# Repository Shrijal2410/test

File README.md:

# Bionic Arm

Our project aims to provide a realistic, functional prosthetic hand for those who have lost theirs. We're not delving into mastering neurology; instead, we're focusing on using muscle sensor data (EMG) to control the hand's movements. Our design is intended for individuals with sufficient remaining limb functionality to provide us with EMG signals, allowing us to move the fingers and wrist accordingly.

## Objectives
Simple enough to outline, but challenging to achieve:

- Create a functional hand with full control over five fingers and wrist movement.
- Ensure the hand can carry up to 1-2kg and grip objects easily.
- Keep the overall weight under 500g, which is a challenge compared to some existing industrial designs.

## Folder Structure
I’ve kept a minimal yet comprehensive folder structure. Ensure each folder has a `README.md`. No spaces in file names use hyphens '-' or underscores '_'. Keep all file and folder names in lowercase. Stick to this template, but feel free to make necessary adjustments.

```
📁 bionicarm
├── 🗃️ bom
│   └── 🗂️ invoice
│   └── 📋 bom.csv
│
├── 🗃️ code
│   └── 🗂️ arduino
│   └── 🗂️ esp32
│   └── 🗂️ raspi
│   └── 🗂️ matlab
│
└── 🗃️ docs
│   └── 🗂️ research
└── 🗃️ electrical
└── 🗃️ mechanical
```

## Commit Message
Keep it clean and meaningful. Use the following structure, and ensure the commit messages are in lowercase:

```
function(dir or subdir/file name): meaningful message

- additional info
- try to use bullet points

e.g., update(electrical): change pi pins for easier wiring

- to minimize the use of vias
```

Stick to this format. If not, I might use git rebase to change your commit message, which could list me as a contributor to that commit. I don’t want to take credit for your work.

## License
Not my area of expertise. So, I’m leaving this part to someone else.

**Note:** The goal of this README is to provide an overview of the project and guide users on where to go. Keep its purpose in mind while updating.

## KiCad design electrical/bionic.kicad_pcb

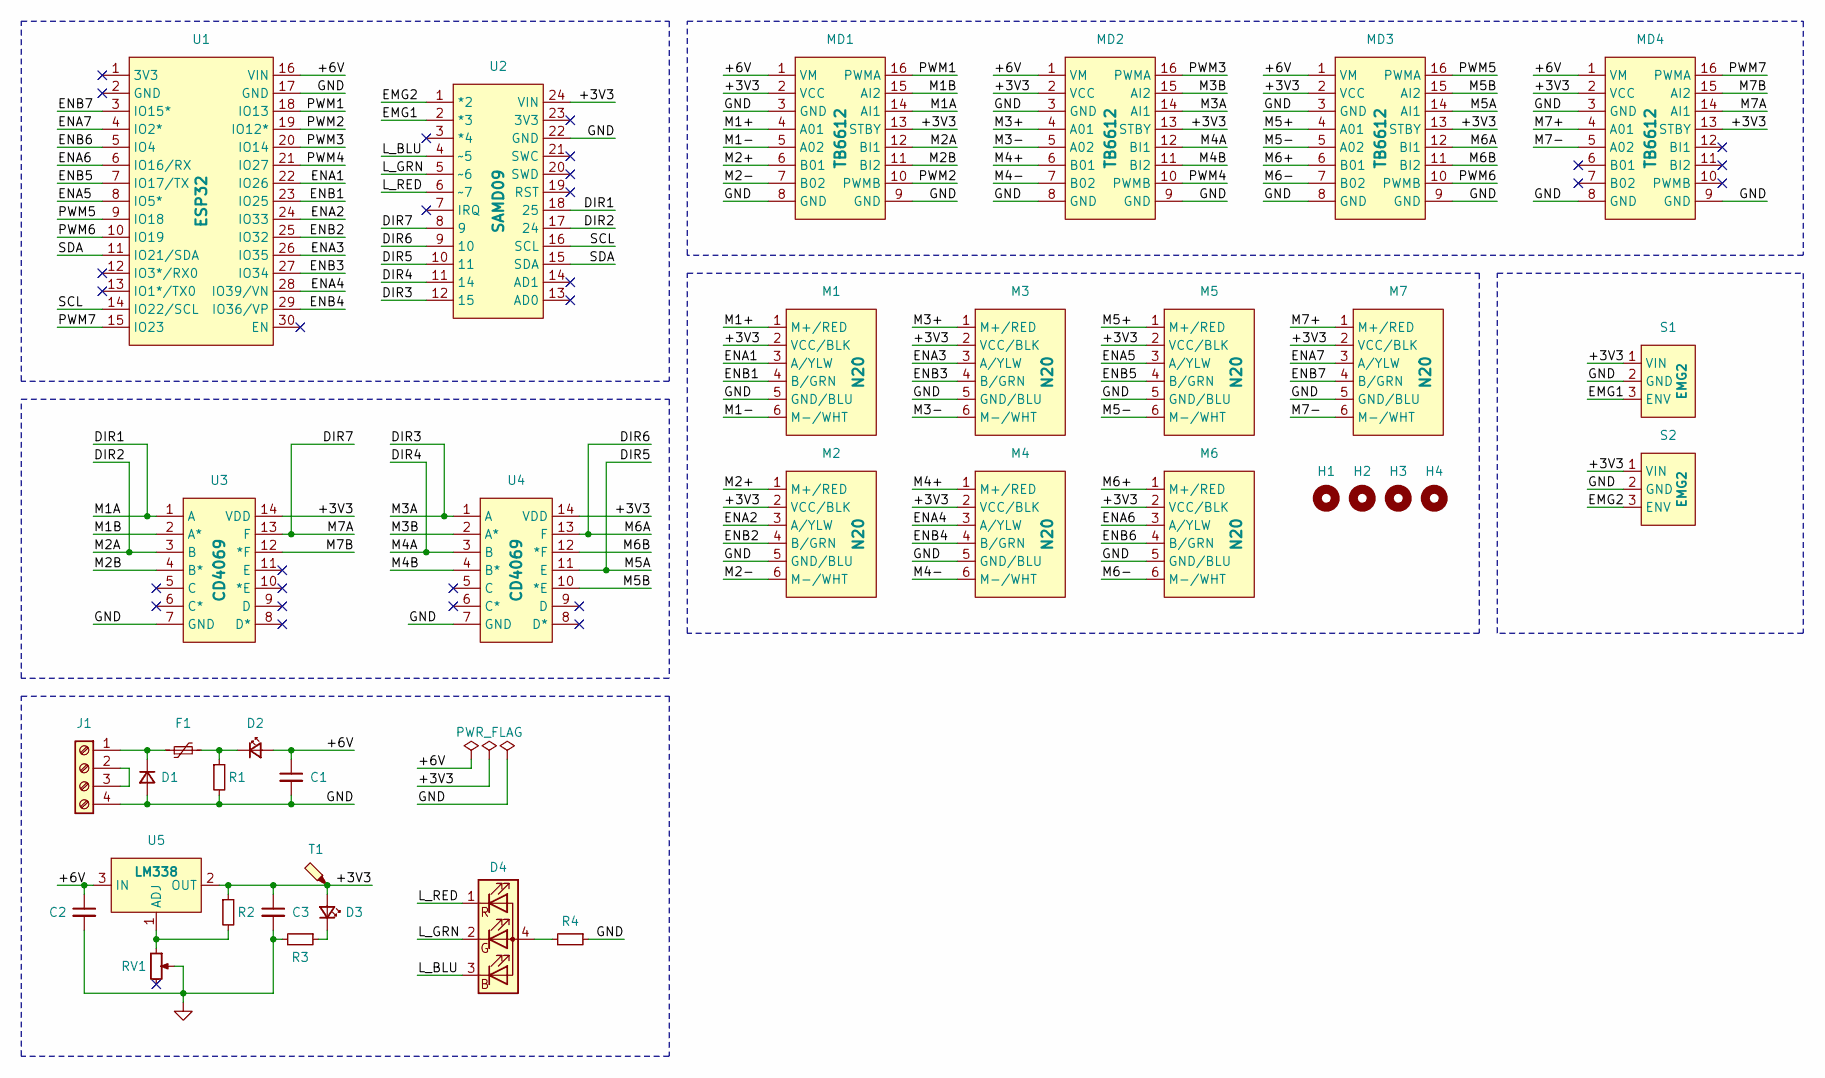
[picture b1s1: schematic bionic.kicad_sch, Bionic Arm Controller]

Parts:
C1, C2, C3: C_Small; CP_Radial_D4.0mm_P2.00mm
D1: D_Small; D_DO-35_SOD27_P7.62mm_Horizontal
D2, D3: LED_Small; LED_D5.0mm_Horizontal_O1.27mm_Z3.0mm
D4: LED_RGBA; LED_D5.0mm-4_RGB
F1: Polyfuse_Small; RGEF500
H1, H2, H3, H4: MountingHole; MountingHole_3.2mm_M3
J1: Screw_Terminal_01x04; TerminalBlock_Phoenix_MKDS-1,5-4-5.08_1x04_P5.08mm_Horizont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
M1, M2, M3, M4, M5, M6, M7: N20; JST_1x06_P2.54mm_Vertical
MD1, MD2, MD3, MD4: TB6612
R1, R2, R3, R4: R_Small; R_Axial_DIN0207_L6.3mm_D2.5mm_P7.62mm_Horizontal
RV1: R_Potentiometer_Small; Potentiometer_Runtron_RM-065_Vertical
S1, S2: EMG2; JST_1x03_P2.54mm_Vertical
T1: TestPoint_Probe; TestPoint_Pad_1.0x1.0mm
U1: ESP32
U2: SAMD09
U3, U4: CD4069
U5: LM338; PinHeader_1x03_P2.54mm_Vertical

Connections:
/+3V3: C3.1, D3.2 (A), M1.2 (VCC/BLK), M2.2 (VCC/BLK), M3.2 (VCC/BLK), M4.2 (VCC/BLK), M5.2 (VCC/BLK), M6.2 (VCC/BLK), M7.2 (VCC/BLK), MD1.2 (VCC), MD1.13 (STBY), MD2.2 (VCC), MD2.13 (STBY), MD3.2 (VCC), MD3.13 (STBY), MD4.2 (VCC), MD4.13 (STBY), R2.1, S1.1 (VIN), S2.1 (VIN), T1.1, U2.24 (VIN), U3.14 (VDD), U4.14 (VDD), U5.2 (OUT)
/+6V: C1.1, C2.1, D2.2 (A), MD1.1 (VM), MD2.1 (VM), MD3.1 (VM), MD4.1 (VM), U1.16 (VIN), U5.3 (IN)
/DIR1: MD1.14 (AI1), U2.18 (25), U3.1 (A)
/DIR2: MD1.12 (BI1), U2.17 (24), U3.3 (B)
/DIR3: MD2.14 (AI1), U2.12 (15), U4.1 (A)
/DIR4: MD2.12 (BI1), U2.11 (14), U4.3 (B)
/DIR5: MD3.14 (AI1), U2.10 (11), U4.11 (E)
/DIR6: MD3.12 (BI1), U2.9 (10), U4.13 (F)
/DIR7: MD4.14 (AI1), U2.8 (9), U3.13 (F)
/EMG1: S1.3 (ENV), U2.2 (*3)
/EMG2: S2.3 (ENV), U2.1 (*2)
/ENA1: M1.3 (A/YLW), U1.22 (IO26)
/ENA2: M2.3 (A/YLW), U1.24 (IO33)
/ENA3: M3.3 (A/YLW), U1.26 (IO35)
/ENA4: M4.3 (A/YLW), U1.28 (IO39/VN)
/ENA5: M5.3 (A/YLW), U1.8 (IO5*)
/ENA6: M6.3 (A/YLW), U1.6 (IO16/RX)
/ENA7: M7.3 (A/YLW), U1.4 (IO2*)
/ENB1: M1.4 (B/GRN), U1.23 (IO25)
/ENB2: M2.4 (B/GRN), U1.25 (IO32)
/ENB3: M3.4 (B/GRN), U1.27 (IO34)
/ENB4: M4.4 (B/GRN), U1.29 (IO36/VP)
/ENB5: M5.4 (B/GRN), U1.7 (IO17/TX)
/ENB6: M6.4 (B/GRN), U1.5 (IO4)
/ENB7: M7.4 (B/GRN), U1.3 (IO15*)
/L_BLU: D4.3 (BK), U2.4 (~5)
/L_GRN: D4.2 (GK), U2.5 (~6)
/L_RED: D4.1 (RK), U2.6 (~7)
/M1+: M1.1 (M+/RED), MD1.4 (A01)
/M1-: M1.6 (M-/WHT), MD1.5 (A02)
/M1B: MD1.15 (AI2), U3.2 (A*)
/M2+: M2.1 (M+/RED), MD1.6 (B01)
/M2-: M2.6 (M-/WHT), MD1.7 (B02)
/M2B: MD1.11 (BI2), U3.4 (B*)
/M3+: M3.1 (M+/RED), MD2.4 (A01)
/M3-: M3.6 (M-/WHT), MD2.5 (A02)
/M3B: MD2.15 (AI2), U4.2 (A*)
/M4+: M4.1 (M+/RED), MD2.6 (B01)
/M4-: M4.6 (M-/WHT), MD2.7 (B02)
/M4B: MD2.11 (BI2), U4.4 (B*)
/M5+: M5.1 (M+/RED), MD3.4 (A01)
/M5-: M5.6 (M-/WHT), MD3.5 (A02)
/M5B: MD3.15 (AI2), U4.10 (*E)
/M6+: M6.1 (M+/RED), MD3.6 (B01)
/M6-: M6.6 (M-/WHT), MD3.7 (B02)
/M6B: MD3.11 (BI2), U4.12 (*F)
/M7+: M7.1 (M+/RED), MD4.4 (A01)
/M7-: M7.6 (M-/WHT), MD4.5 (A02)
/M7B: MD4.15 (AI2), U3.12 (*F)
/PWM1: MD1.16 (PWMA), U1.18 (IO13)
/PWM2: MD1.10 (PWMB), U1.19 (IO12*)
/PWM3: MD2.16 (PWMA), U1.20 (IO14)
/PWM4: MD2.10 (PWMB), U1.21 (IO27)
/PWM5: MD3.16 (PWMA), U1.9 (IO18)
/PWM6: MD3.10 (PWMB), U1.10 (IO19)
/PWM7: MD4.16 (PWMA), U1.15 (IO23)
/SCL: U1.14 (IO22/SCL), U2.16 (SCL)
/SDA: U1.11 (IO21/SDA), U2.15 (SDA)
GND: C1.2, C2.2, C3.2, D1.2 (A), J1.4, M1.5 (GND/BLU), M2.5 (GND/BLU), M3.5 (GND/BLU), M4.5 (GND/BLU), M5.5 (GND/BLU), M6.5 (GND/BLU), M7.5 (GND/BLU), MD1.3 (GND), MD1.8 (GND), MD1.9 (GND), MD2.3 (GND), MD2.8 (GND), MD2.9 (GND), MD3.3 (GND), MD3.8 (GND), MD3.9 (GND), MD4.3 (GND), MD4.8 (GND), MD4.9 (GND), R1.2, R3.2, R4.1, RV1.2, S1.2 (GND), S2.2 (GND), U1.17 (GND), U2.22 (GND), U3.7 (GND), U4.7 (GND)
unnamed: D1.1 (K), F1.1, J1.1
unnamed: D2.1 (K), F1.2, R1.1
unnamed: D3.1 (K), R3.1
unnamed: D4.4 (A), R4.2
unnamed: J1.2, J1.3
unnamed: R2.2, RV1.1, U5.1 (ADJ)

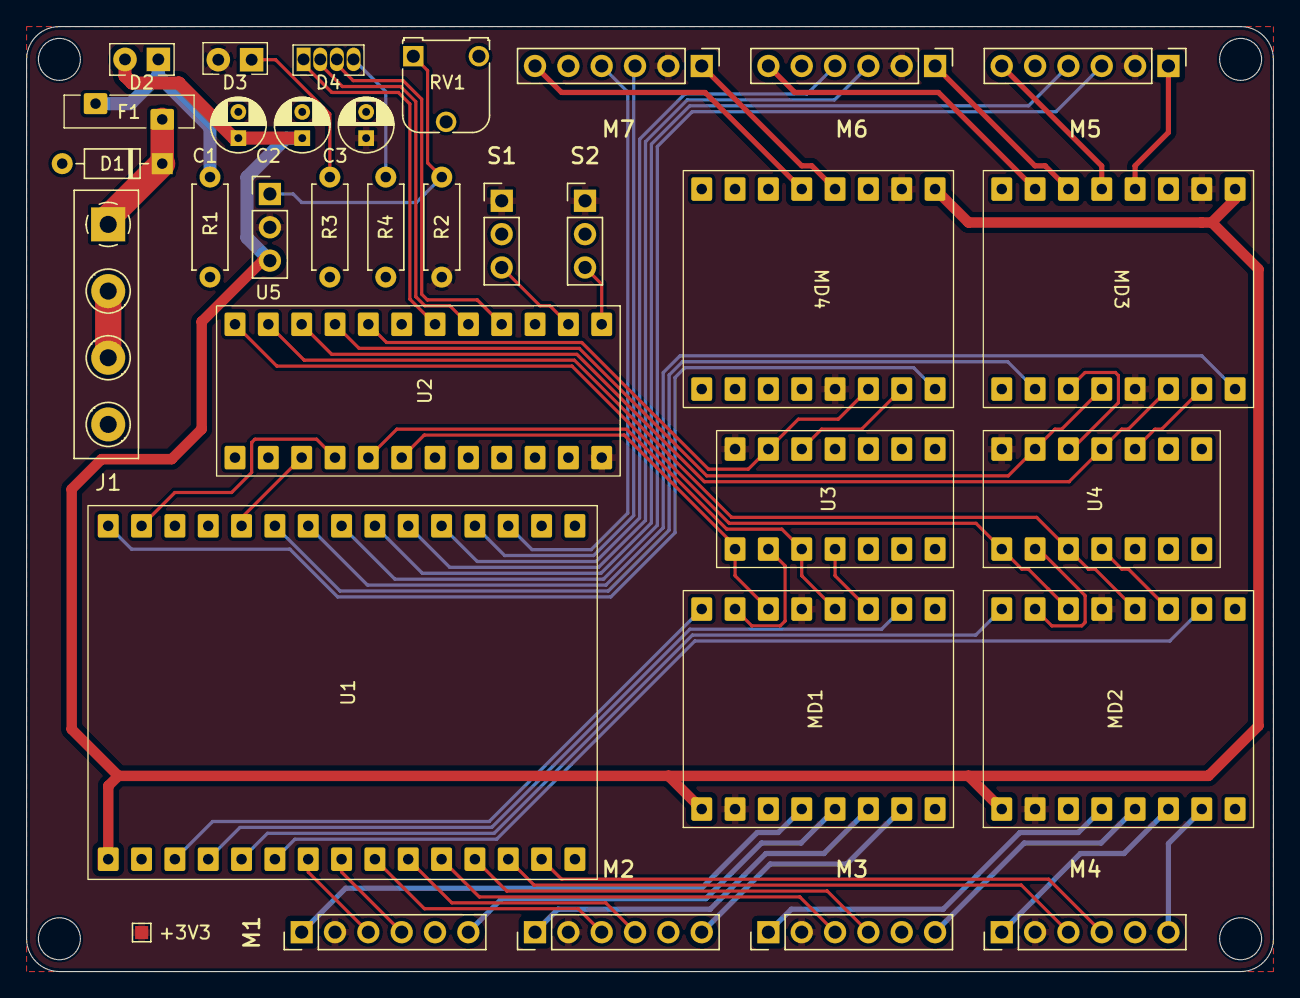
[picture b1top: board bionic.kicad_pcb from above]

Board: 2 copper layers, 95.0 x 72.0 mm, 37 parts (0 on the bottom side), 65 nets.

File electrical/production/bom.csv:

Designator,Footprint,Quantity,Value,LCSC Part #
"C1, C2, C3",CP_Radial_D4.0mm_P2.00mm,3,C_Small,
D1,D_DO-35_SOD27_P7.62mm_Horizontal,1,D_Small,
"D2, D3",LED_D5.0mm_Horizontal_O1.27mm_Z3.0mm,2,LED_Small,
D4,LED_D5.0mm-4_RGB,1,LED_RGBA,
F1,RGEF500,1,Polyfuse_Small,
J1,"TerminalBlock_Phoenix_MKDS-1,5-4-5.08_1x04_P5.08mm_Horizontal",1,Screw_Terminal_01x04,
"M1, M2, M3, M4, M5, M6, M7",JST_1x06_P2.54mm_Vertical,7,N20,
"MD1, MD2, MD3, MD4",TB6612,4,TB6612,
"R1, R2, R3, R4",R_Axial_DIN0207_L6.3mm_D2.5mm_P7.62mm_Horizontal,4,R_Small,
RV1,Potentiometer_Runtron_RM-065_Vertical,1,R_Potentiometer_Small,
"S1, S2",JST_1x03_P2.54mm_Vertical,2,EMG2,
T1,TestPoint_Pad_1.0x1.0mm,1,TestPoint_Probe,
U1,ESP32,1,ESP32,
U2,SAMD09,1,SAMD09,
"U3, U4",CD4069,2,CD4069,
U5,PinHeader_1x03_P2.54mm_Vertical,1,LM338,

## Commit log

2024-07-06 add(readme): guide for commit and folder structure
2024-07-08 add(code/arduino): pid tuning
2024-07-08 add(docs/research): EMG working
2024-07-13 add(electrical): bionicBoard design
2024-07-13 add(electrical/symbol): Updated Components
2024-07-14 update(electrical): bionicBoard 'ERC Passed!'
2024-07-16 add(electrical/footprint): Updated Footprints
2024-07-16 update(electrical): All Footprint Assigned!
2024-07-16 update(electrical/pcb): signal wiring Complete!!
2024-07-17 update(electrical/pcb): DRC Passed! and Updated 3D-Models
2024-07-17 update(electrical/pcb): Updated Placement and Reduce Board
2024-07-18 update(electrical/pcb): Finialized v1.0 Design
2024-07-21 add(code): esp32 ui & motorpid code
2024-07-21 add(data): sensor data acquisition and processing
2024-07-22 add(code/simulink): simulation files
2024-07-22 add(mechanical/stl): design stl files
2024-07-22 add(code): minor tests for integration
2024-07-27 refactor(structure): rename and reorganize folders and files
2024-07-31 add(data/sim): Add plots for hand and wrist simulations
2024-07-31 add(code/opencv): Add scripts for grasping and finger control
2024-08-08 add(code): test codes using esp32 with seesaw
2024-08-08 add(code): Build code for Bionic Arm with ESP32 and Seesaw integration
